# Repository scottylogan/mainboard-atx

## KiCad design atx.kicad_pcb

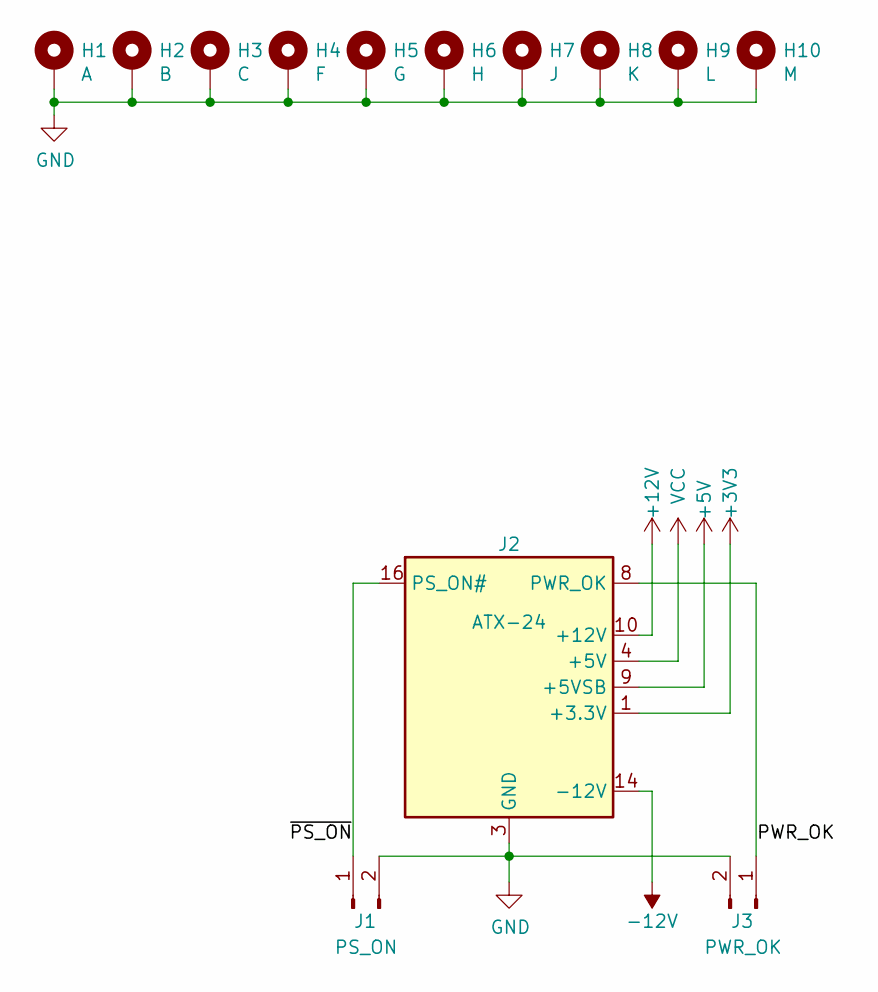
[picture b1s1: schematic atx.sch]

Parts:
H1: A; MountingHole_4.3mm_M4_Pad
H2: B; MountingHole_4.3mm_M4_Pad
H3: C; MountingHole_4.3mm_M4_Pad
H4: F; MountingHole_4.3mm_M4_Pad
H5: G; MountingHole_4.3mm_M4_Pad
H6: H; MountingHole_4.3mm_M4_Pad
H7: J; MountingHole_4.3mm_M4_Pad
H8: K; MountingHole_4.3mm_M4_Pad
H9: L; MountingHole_4.3mm_M4_Pad
H10: M; MountingHole_4.3mm_M4_Pad
J1: PS_ON; JST_PH_B2B-PH-K_1x02_P2.00mm_Vertical
J2: ATX-24; Molex_Mini-Fit_Jr_5566-24A_2x12_P4.20mm_Vertical
J3: PWR_OK; JST_PH_B2B-PH-K_1x02_P2.00mm_Vertical

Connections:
+3V3: J2.1 (+3.3V), J2.2 (+3.3V), J2.12 (+3.3V), J2.13 (+3.3V)
+5V: J2.9 (+5VSB)
+12V: J2.10 (+12V), J2.11 (+12V)
-12V: J2.14 (-12V)
/PWR_OK: J2.8 (PWR_OK), J3.1
/~PS_ON: J1.1, J2.16 (PS_ON#)
GND: H1.1, H2.1, H3.1, H4.1, H5.1, H6.1, H7.1, H8.1, H9.1, H10.1, J1.2, J2.3 (GND), J2.5 (GND), J2.7 (GND), J2.15 (GND), J2.17 (GND), J2.18 (GND), J2.19 (GND), J2.24 (GND), J3.2
VCC: J2.4 (+5V), J2.6 (+5V), J2.21 (+5V), J2.22 (+5V), J2.23 (+5V)

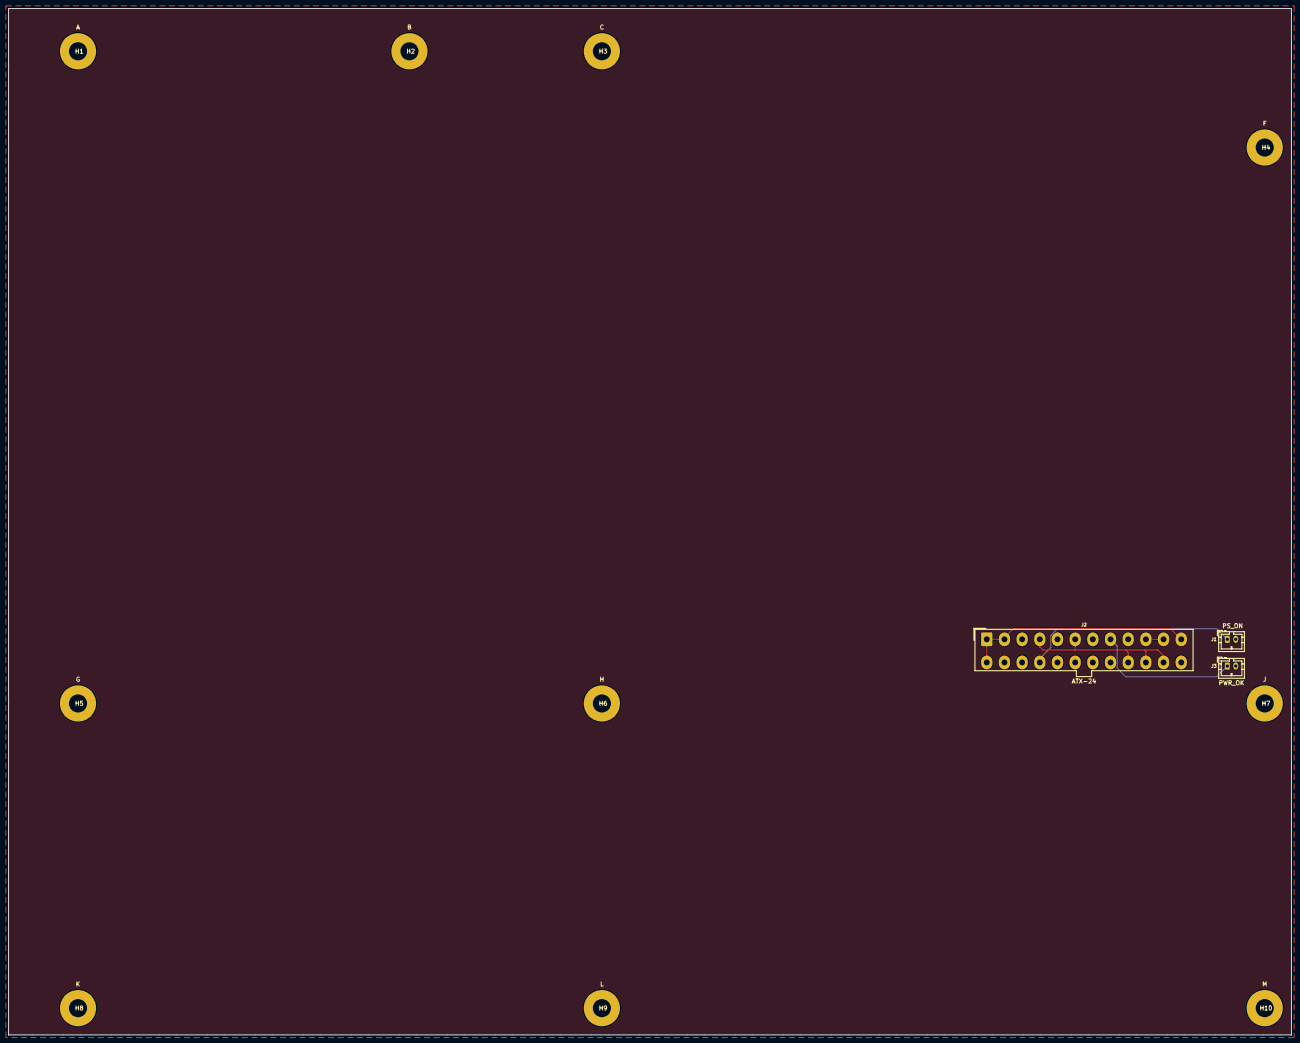
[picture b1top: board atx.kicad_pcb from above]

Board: 2 copper layers, 304.8 x 243.8 mm, 13 parts (0 on the bottom side), 6 nets.

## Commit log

2021-10-30 initial version
2025-04-16 added LICENSE
